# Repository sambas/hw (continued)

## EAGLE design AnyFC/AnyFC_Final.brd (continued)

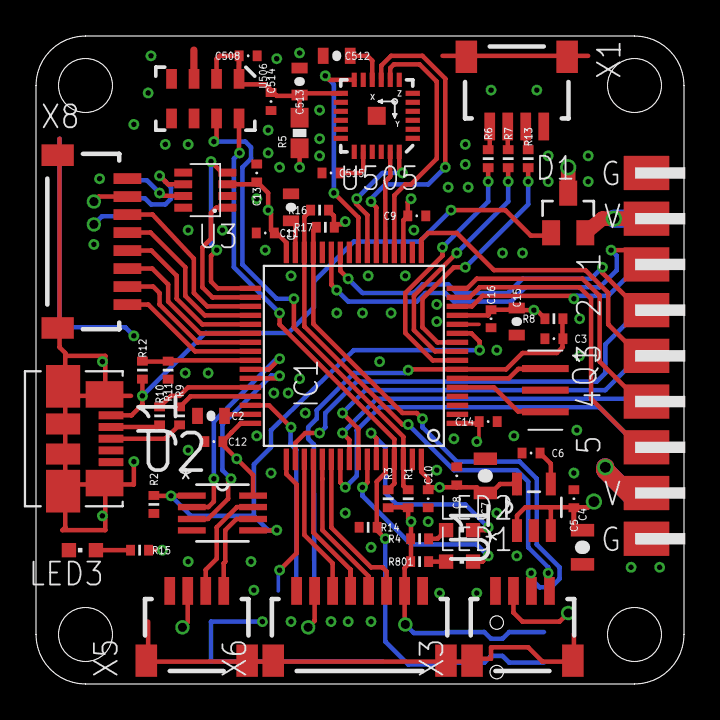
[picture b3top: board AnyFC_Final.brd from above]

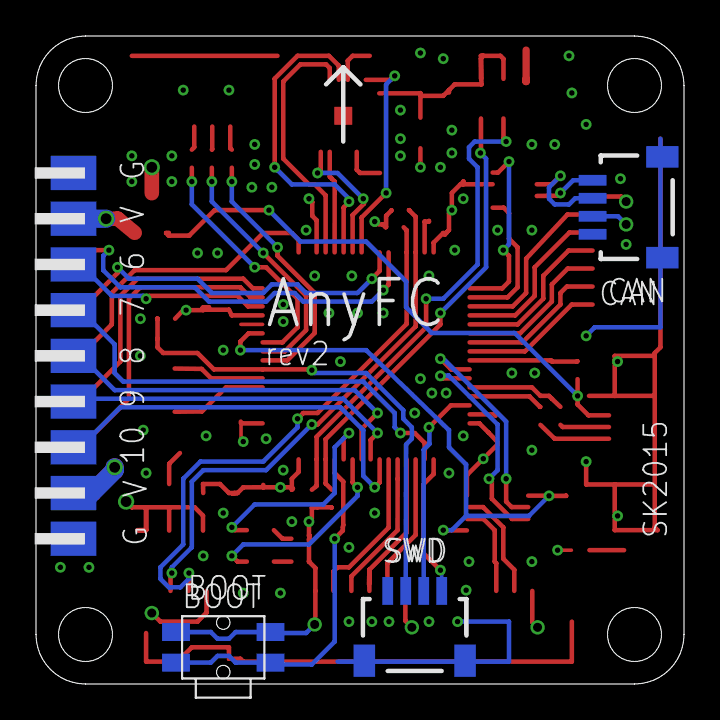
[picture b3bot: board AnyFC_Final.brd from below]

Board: 4 copper layers, 36.0 x 36.0 mm, 60 parts (3 on the bottom side), 71 nets.

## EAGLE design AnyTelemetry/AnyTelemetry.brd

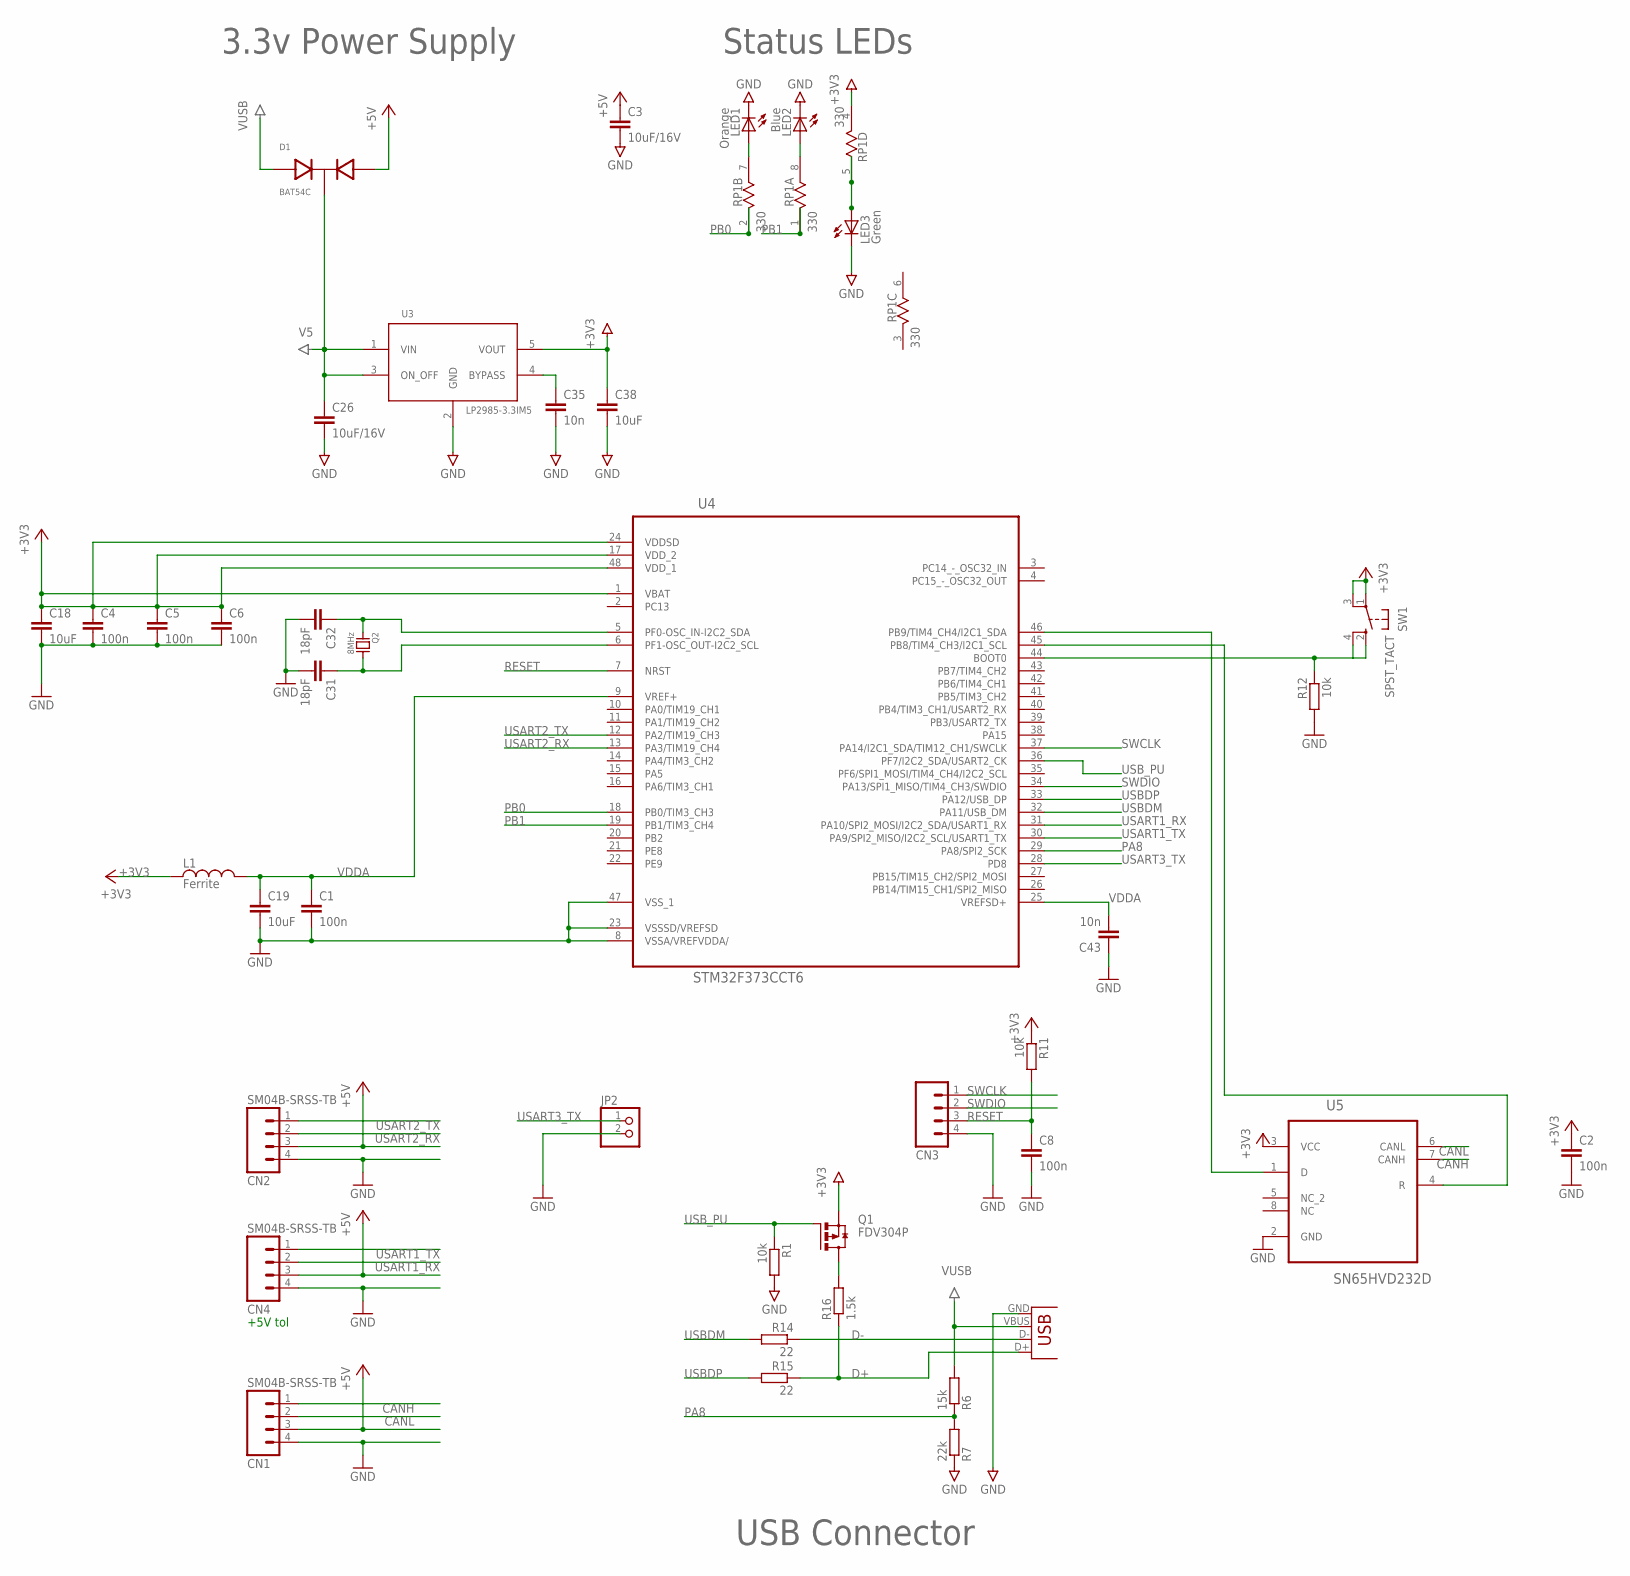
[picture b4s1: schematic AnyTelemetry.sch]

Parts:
C1, C2, C4, C5, C6, C8: 100n; 0603
C3, C26: 10uF/16V; C0805
C18, C19, C38: 10uF; C0805
C31, C32: 18pF; 0603
C35: 10n; C0603
C43: 10n; 0603-CAP
CN1, CN2, CN3, CN4: SM04B-SRSS-TB
D1: BAT54C; SOT23
JP2: PINHD-1X02_2.54-S; 1X02-S
L1: Ferrite; 0603
LED1: Orange; CHIPLED_0603
LED2: Blue; CHIPLED_0603
LED3: Green; CHIPLED_0603
Q1: FDV304P; SUPER-SOT3
Q2: 8MHz; CRYSTAL-5X3
R1, R11, R12: 10k; R0603
R6: 15k; R0603
R7: 22k; R0603
R14, R15: 22; R0603
R16: 1.5k; R0603
RP1: 330; RES4NT
SW1: SPST_TACT; EVQ-PU
U3: LP2985-3.3IM5; SOT23-5
U4: STM32F373CCT6; QFP50P900X900X160-48N
U5: SN65HVD232D; SOIC127P600X175-8N
X2: USBSMD; USB-MINIB

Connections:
+3V3: C2.1, C4.1, C5.1, C6.1, C18.1, C38.1, L1.1, Q1.2 (S), R11.1, RP1.4 (1), SW1.1, SW1.3 (P1), U3.5 (VOUT), U4.1 (VBAT), U4.17 (VDD_2), U4.24 (VDDSD), U4.48 (VDD_1), U5.3 (VCC)
+5V: C3.1, CN1.3, CN2.3, CN4.3, D1.2
BOOT0: R12.1, SW1.2 (S), SW1.4 (S1), U4.44 (BOOT0)
CANH: CN1.1, U5.7 (CANH)
CANL: CN1.2, U5.6 (CANL)
D+: R15.1, R16.1, X2.D+
D-: R14.1, X2.D-
GND: C1.2, C2.2, C3.2, C4.2, C5.2, C6.2, C8.2, C18.2, C19.2, C26.2, C31.2, C32.2, C35.2, C38.2, C43.1, CN1.4, CN2.4, CN3.4, CN4.4, JP2.2, LED1.C, LED2.C, LED3.C, R1.2, R7.1, R12.2, U3.2 (GND), U4.8 (VSSA/VREFVDDA/), U4.23 (VSSSD/VREFSD), U4.47 (VSS_1), U5.2 (GND), X2.GND
unnamed: Q1.3 (D), R16.2
unnamed: LED1.A, RP1.7 (2)
unnamed: LED2.A, RP1.8 (2)
unnamed: LED3.A, RP1.5 (2)
unnamed: C31.1, Q2.3 (2), U4.6 (PF1-OSC_OUT-I2C2_SCL)
unnamed: C32.1, Q2.1, U4.5 (PF0-OSC_IN-I2C2_SDA)
unnamed: C35.1, U3.4 (BYPASS)
PA8: R6.1, R7.2, U4.29 (PA8/SPI2_SCK)
PB0: RP1.2 (1), U4.18 (PB0/TIM3_CH3)
PB1: RP1.1, U4.19 (PB1/TIM3_CH4)
RESET: C8.1, CN3.3, R11.2, U4.7 (NRST)
RXCAN: U4.45 (PB8/TIM4_CH3/I2C1_SCL), U5.4 (R)
SWCLK: CN3.1, U4.37 (PA14/I2C1_SDA/TIM12_CH1/SWCLK)
SWDIO: CN3.2, U4.34 (PA13/SPI1_MISO/TIM4_CH3/SWDIO)
TXCAN: U4.46 (PB9/TIM4_CH4/I2C1_SDA), U5.1 (D)
USART1_RX: CN4.2, U4.31 (PA10/SPI2_MOSI/I2C2_SDA/USART1_RX)
USART1_TX: CN4.1, U4.30 (PA9/SPI2_MISO/I2C2_SCL/USART1_TX)
USART2_RX: CN2.2, U4.13 (PA3/TIM19_CH4)
USART2_TX: CN2.1, U4.12 (PA2/TIM19_CH3)
USART3_TX: JP2.1, U4.28 (PD8)
USBDM: R14.2, U4.32 (PA11/USB_DM)
USBDP: R15.2, U4.33 (PA12/USB_DP)
USB_PU: Q1.1 (G), R1.1, U4.36 (PF7/I2C2_SDA/USART2_CK)
V5: C26.1, D1.3, U3.1 (VIN), U3.3 (ON_OFF)
VDDA: C1.1, C19.1, C43.2, L1.2, U4.9 (VREF+), U4.25 (VREFSD+)
VUSB: D1.1, R6.2, X2.VBUS

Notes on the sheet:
USB Connector
3.3v Power Supply
Status LEDs
+5V tol

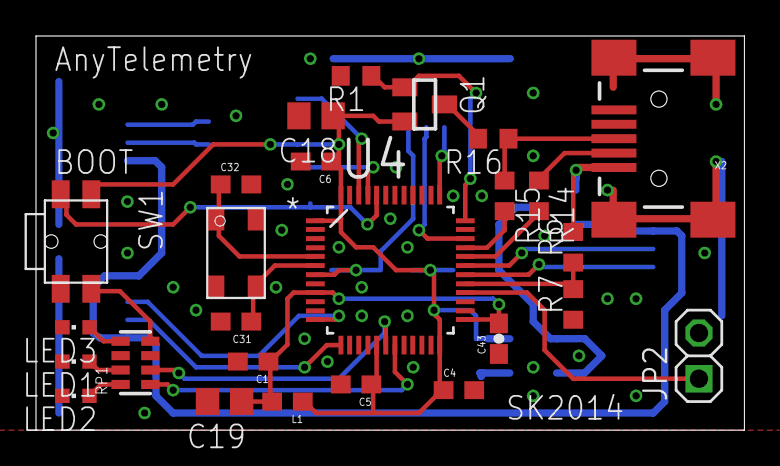
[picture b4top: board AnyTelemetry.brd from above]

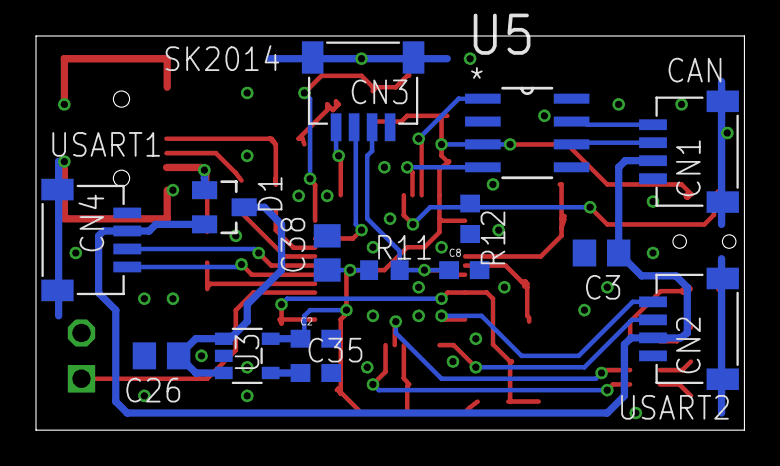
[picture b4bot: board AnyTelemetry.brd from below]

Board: 2 copper layers, 39.4 x 21.9 mm, 41 parts (15 on the bottom side), 34 nets.

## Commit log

2015-10-01 Add Projects
2015-10-01 CC license
2015-10-01 Add images
2016-10-29 AnyFC-F7
2017-04-14 Add STM32F722 design
